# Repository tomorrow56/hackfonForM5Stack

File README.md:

# hackfonForM5Stack

「hackfon」とは「アナログ電話をスマートリモコンに」というコンセプトで「FutuRocket株式会社」 (https://www.futurocket.co/) が現在製品化に向けて進めているIoTプロダクトです。

以下に簡単な製品説明があります。<br>
(技術書典#8の"Madamada M5Stack Moku Moku Mook β" ( https://booth.pm/ja/items/1887481 )からの抜粋版です)<br>

/techbookfesta8/tomorrow56_tech8_03.md

### 2020年4月13日更新

"exsample"にIFTTT対応版を追加しました。<br>

#### /example/M5_hackfon_IFTTT

同梱の "hackfon.cfg" を編集して "makerKey"と"Event trigger"を設定に応じて書き換えてSDカードのルートに置けば設定をこちらから読みますので、ソースを修正する必要はありません。今回のバージョンでは各キーに１つのIFTTTのイベントキーが割り当てることができます。<br><br>

また、コンパイル済のバイナリー(M5-SD-Updater対応版, M5_hackfon_IFTTT.bin) も準備しました。<br>
こちらをSDカードのルートに置いて、以下のM5Burnerをダウンロードして、LovyanLauncher-v0.2.3 を本体に書き込めばSDカードに保存したバイナリーを実行することができます。<br>
https://m5stack.oss-cn-shenzhen.aliyuncs.com/resource/software/M5Burner.zip

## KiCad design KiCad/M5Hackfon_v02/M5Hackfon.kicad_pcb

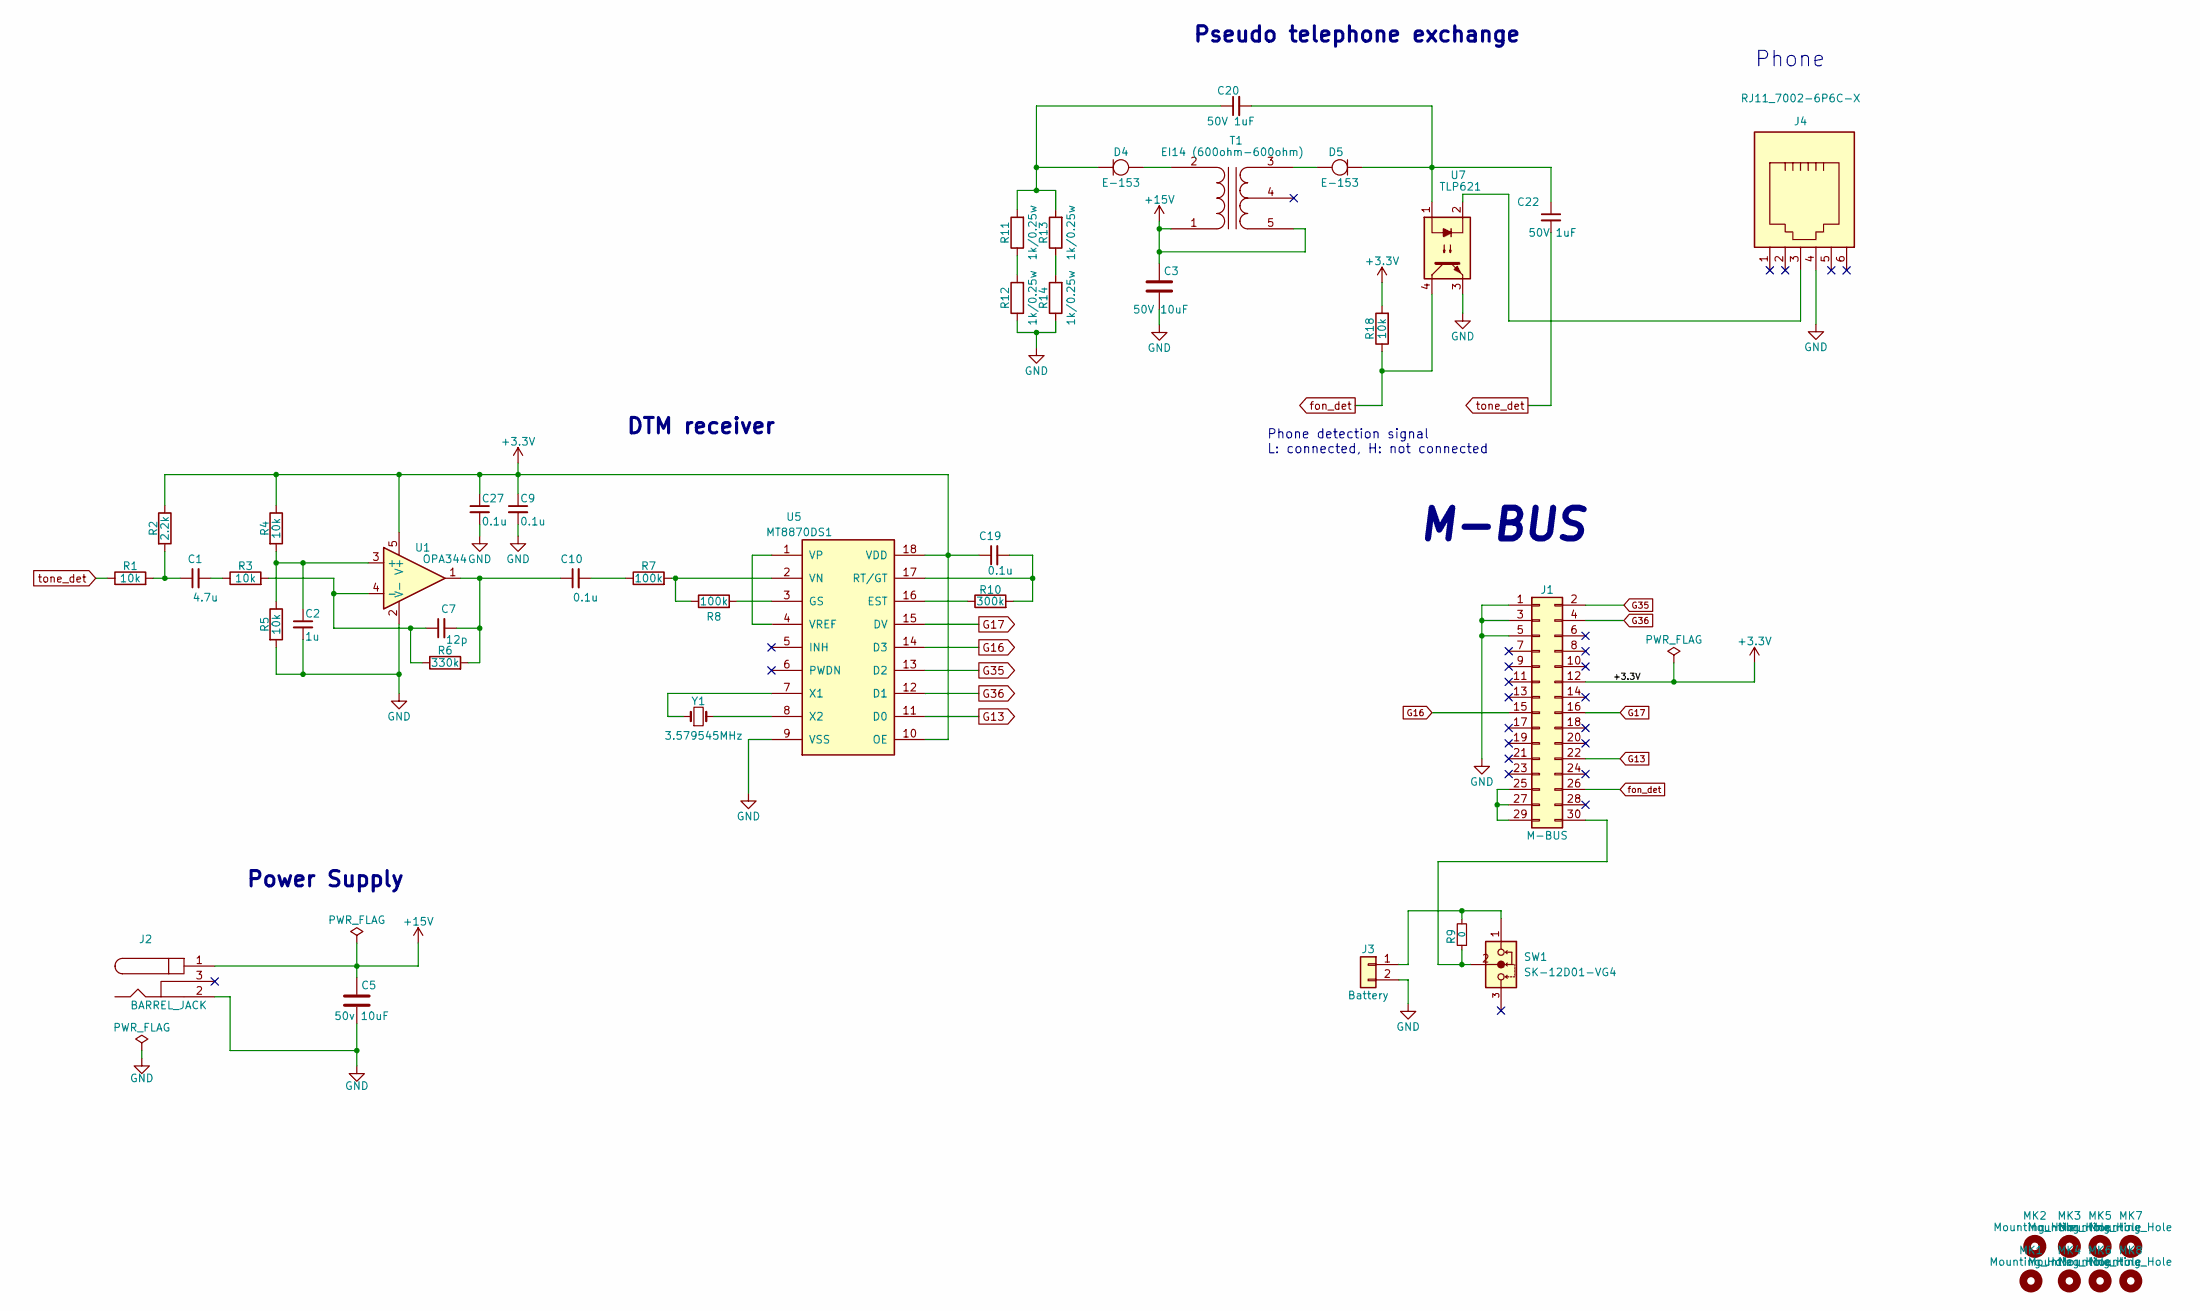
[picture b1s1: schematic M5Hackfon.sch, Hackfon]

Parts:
C1: 4.7u; C_0603
C2: 1u; C_0603
C3: 50V 10uF; C_0603
C5: 50v 10uF; C_0603
C7: 12p; C_0603
C9, C10, C19, C27: 0.1u; C_0603
C20, C22: 50V 1uF; C_0603
D4, D5: E-153; D_T-1_P5.08mm_Horizontal
J1: M-BUS; Pin_Header_MBUS_SMD_TH
J2: BARREL_JACK
J3: Battery; Pin_Header_Angled_1x02_Pitch2.54mm
J4: RJ11_7002-6P6C-X
MK1, MK2, MK3, MK4: Mounting_Hole; MountingHole_3.2mm_M3
MK5, MK6, MK7, MK8: Mounting_Hole; MountingHole_2.2mm_M2
R1, R3, R4, R5, R18: 10k; R_0603
R2: 2.2k; R_0603
R6: 330k; R_0603
R7, R8: 100k; R_0603
R9: 0; R_0603
R10: 300k; R_0603
R11, R12, R13, R14: 1k/0.25w; R_0805
SW1: SK-12D01-VG4; slide_switch_angled
T1: EI14 (600ohm-600ohm); TRANS_EI14
U1: OPA344; SOT-23-5
U5: MT8870DS1; SOIC-18W_7.5x11.6mm_Pitch1.27mm
U7: TLP621; DIP-4_W7.62mm
Y1: 3.579545MHz; Crystal_HC49-U_Vertical

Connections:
+3V3: C9.1, C19.1, C27.1, J1.12, R2.1, R4.1, R18.2, U1.5 (V+), U5.10 (OE), U5.18 (VDD)
+15V: C3.1, C5.1, J2.1, T1.1 (AA), T1.5 (SB)
G13: J1.22, U5.11 (D0)
G16: J1.15, U5.14 (D3)
G17: J1.16, U5.15 (DV)
G35: J1.2, U5.13 (D2)
G36: J1.4, U5.12 (D1)
GND: C2.2, C3.2, C5.2, C9.2, C27.2, J1.1, J1.3, J1.5, J2.2, J3.2, J4.4, R5.2, R12.1, R14.1, U1.2 (V-), U5.9 (VSS), U7.3
unnamed: C1.1, R1.2, R2.2
unnamed: C1.2, R3.1
unnamed: C2.1, R4.2, R5.1, U1.3 (+)
unnamed: C7.1, R3.2, R6.1, U1.4 (-)
unnamed: C7.2, C10.1, R6.2, U1.1
unnamed: C10.2, R7.1
unnamed: C19.2, R10.2, U5.17 (RT/GT)
unnamed: C20.1, D4.1 (K), R11.2, R13.2
unnamed: C20.2, C22.1, D5.1 (K), U7.1
unnamed: D4.2 (A), T1.2 (AB)
unnamed: D5.2 (A), T1.3 (SA)
unnamed: J1.25, J1.27, J1.29
unnamed: J1.30, R9.1, SW1.2
unnamed: J3.1, R9.2, SW1.1
unnamed: J4.3, U7.2
unnamed: R7.2, R8.1, U5.2 (VN)
unnamed: R8.2, U5.3 (GS)
unnamed: R10.1, U5.16 (EST)
unnamed: R11.1, R12.2
unnamed: R13.1, R14.2
unnamed: U5.1 (VP), U5.4 (VREF)
unnamed: U5.7 (X1), Y1.1
unnamed: U5.8 (X2), Y1.2
fon_det: J1.26, R18.1, U7.4
tone_det: C22.2, R1.1

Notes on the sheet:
Power Supply
Phone
Pseudo telephone exchange
Phone detection signal L: connected, H: not connected
DTM receiver
M-BUS

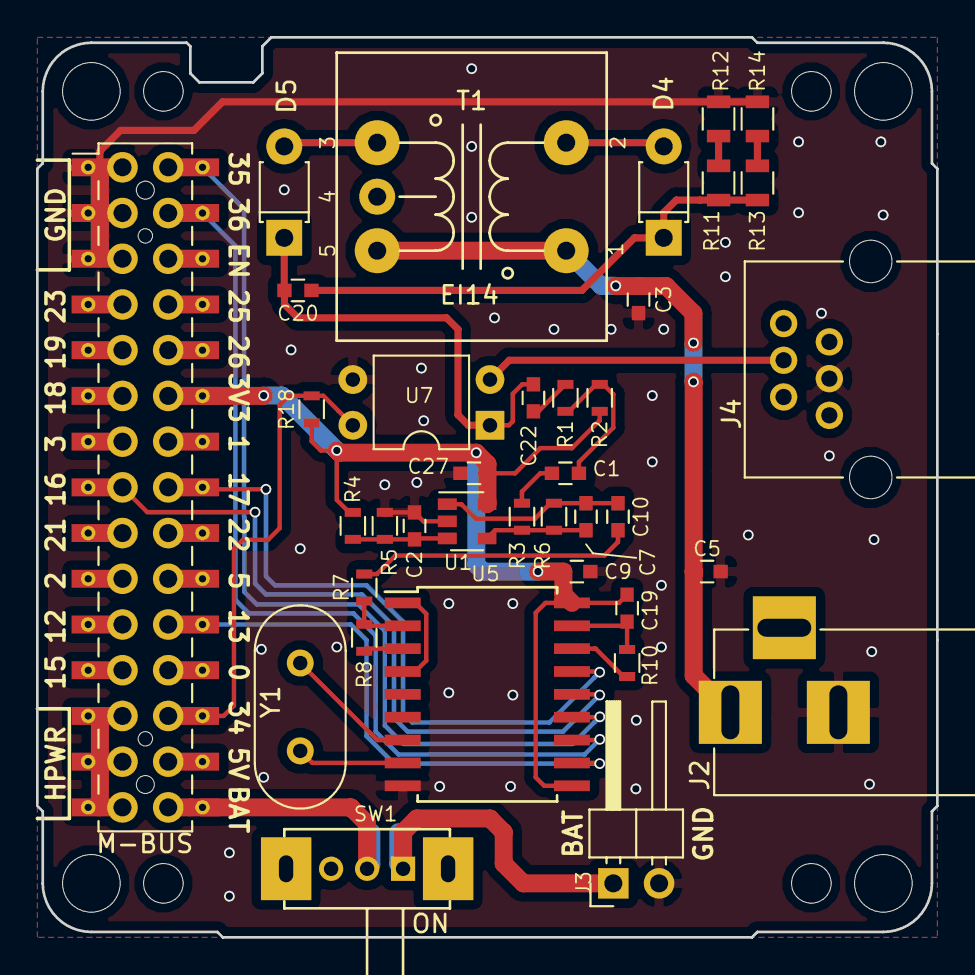
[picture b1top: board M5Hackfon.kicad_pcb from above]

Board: 2 copper layers, 50.0 x 50.0 mm, 46 parts (1 on the bottom side), 33 nets.

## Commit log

2020-02-25 初稿の確認依頼用
2020-02-25 Link修正
2020-03-08 add tentative case data
2020-03-08 add Cad data
2020-03-08 add pcb gerber data
2020-03-08 add gerber data
2020-03-08 add drawings of main parts
2020-03-16 add sample code
2020-04-13 add case data
2020-04-13 sample sketch for IFTTT v02
2020-04-13 Review the folder structure
